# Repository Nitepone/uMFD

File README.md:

# uMFD: A small button pad for Pico

This is a version 1.0 of my small mfd controller.

This repo contains the blender files for the case, along with kicad files for
the button carrier PCB, and the source code for the gamepad software.

The completed project appears as an xinput device where each of the 20 buttons
it its own digital input.

## Building

1. `mkdir build`
2. `cmake -B build`
3. `make -C build`
4. "Where is the final image?"
5. `find -name '*.uf2'`

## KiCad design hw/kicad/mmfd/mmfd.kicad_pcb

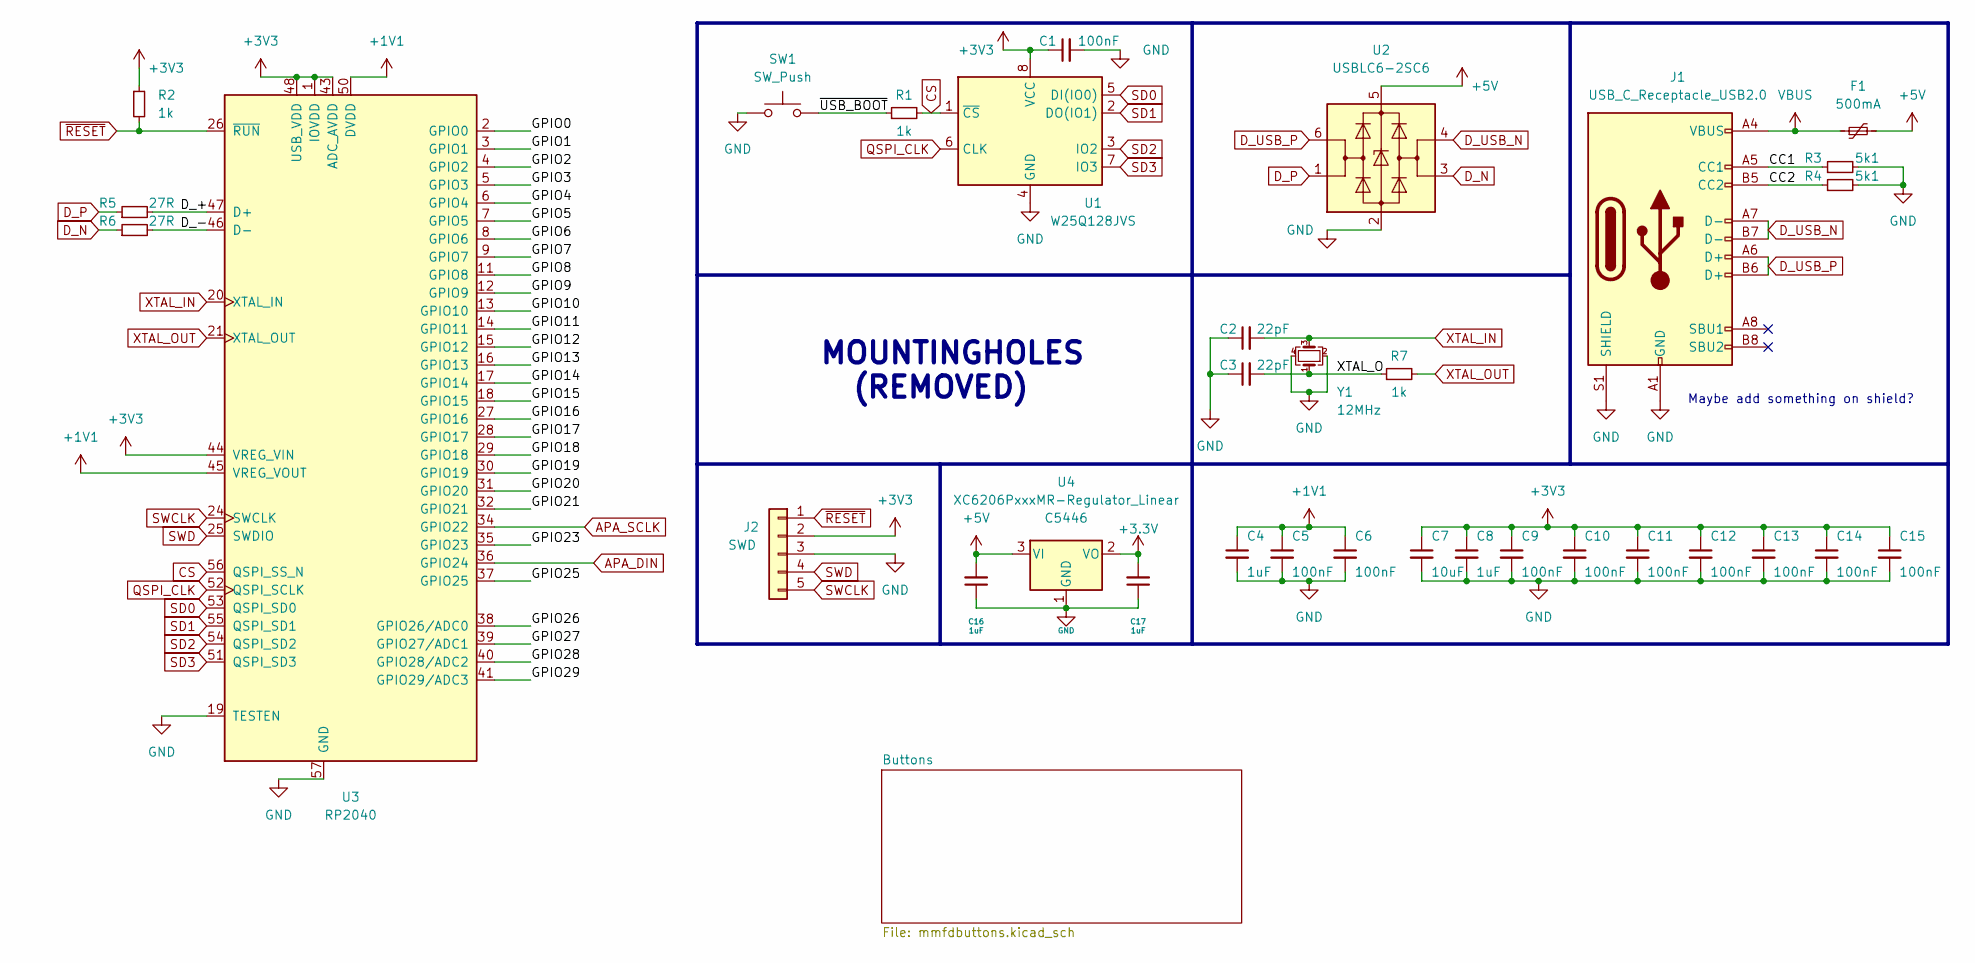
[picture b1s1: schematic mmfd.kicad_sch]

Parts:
C1, C5, C6, C9, C10, C11, C12, C13, C14, C15: 100nF; C_0402_1005Metric; LCSC C1525
C2, C3: 22pF; C_0402_1005Metric; LCSC C1555
C4, C8, C16, C17: 1uF; C_0402_1005Metric; LCSC C52923
C7: 10uF; C_0402_1005Metric; LCSC C15525
F1: 500mA; Fuse_1206_3216Metric; LCSC C70076
J1: USB_C_Receptacle_USB2.0; USB_C_Receptacle_HRO_TYPE-C-31-M-12; LCSC C165948
J2: SWD; PinSocket_1x05_P2.54mm_Vertical
R1, R2, R7: 1k; R_0402_1005Metric; LCSC C11702
R3, R4: 5k1; R_0402_1005Metric; LCSC C25905
R5, R6: 27R; R_0603_1608Metric; LCSC C25190
SW1: SW_Push; PinSocket_1x02_P2.54mm_Vertical
U1: W25Q128JVS; SOIC-8_5.23x5.23mm_P1.27mm; LCSC C131025
U2: USBLC6-2SC6; SOT-23-6; LCSC C2827654
U3: RP2040; RP2040-QFN-56; LCSC C2040
U4: XC6206PxxxMR-Regulator_Linear; SOT-23; LCSC C5446
Y1: 12MHz; Crystal_SMD_3225-4Pin_3.2x2.5mm; LCSC C9002

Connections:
+1V1: C4.1, C5.1, C6.1, U3.23 (DVDD), U3.45 (VREG_VOUT), U3.50 (DVDD)
+5V: C16.2, F1.2, U2.5 (VBUS), U4.3 (VI); also elsewhere on the board
/CC1: J1.A5 (CC1), R3.1
/CC2: J1.B5 (CC2), R4.1
/D_+: R5.2, U3.47 (D+)
/D_-: R6.2, U3.46 (D-)
/GPIO0: U3.2 (GPIO0)
/GPIO1: U3.3 (GPIO1)
/GPIO2: U3.4 (GPIO2)
/GPIO3: U3.5 (GPIO3)
/GPIO4: U3.6 (GPIO4)
/GPIO5: U3.7 (GPIO5)
/GPIO6: U3.8 (GPIO6)
/GPIO7: U3.9 (GPIO7)
/GPIO8: U3.11 (GPIO8)
/GPIO9: U3.12 (GPIO9)
/GPIO10: U3.13 (GPIO10)
/GPIO11: U3.14 (GPIO11)
/GPIO12: U3.15 (GPIO12)
/GPIO13: U3.16 (GPIO13)
/GPIO14: U3.17 (GPIO14)
/GPIO15: U3.18 (GPIO15)
/GPIO16: U3.27 (GPIO16)
/GPIO17: U3.28 (GPIO17)
/GPIO18: U3.29 (GPIO18)
/GPIO19: U3.30 (GPIO19)
/GPIO20: U3.31 (GPIO20)
/GPIO21: U3.32 (GPIO21)
/GPIO23: U3.35 (GPIO23)
/GPIO25: U3.37 (GPIO25)
/GPIO26: U3.38 (GPIO26/ADC0)
/GPIO27: U3.39 (GPIO27/ADC1)
/GPIO28: U3.40 (GPIO28/ADC2)
/GPIO29: U3.41 (GPIO29/ADC3)
/XTAL_O: C3.2, R7.1, Y1.1
APA_DIN: U3.36 (GPIO24); also elsewhere on the board
APA_SCLK: U3.34 (GPIO22); also elsewhere on the board
CS: R1.2, U1.1 (~CS), U3.56 (QSPI_SS_N)
D_N: R6.1, U2.3 (I/O2)
D_P: R5.1, U2.1 (I/O1)
D_USB_N: J1.A7 (D-), J1.B7 (D-), U2.4 (I/O2)
D_USB_P: J1.A6 (D+), J1.B6 (D+), U2.6 (I/O1)
QSPI_CLK: U1.6 (CLK), U3.52 (QSPI_SCLK)
SD0: U1.5 (DI(IO0)), U3.53 (QSPI_SD0)
SD1: U1.2 (DO(IO1)), U3.55 (QSPI_SD1)
SD2: U1.3 (IO2), U3.54 (QSPI_SD2)
SD3: U1.7 (IO3), U3.51 (QSPI_SD3)
SWCLK: J2.5, U3.24 (SWCLK)
SWD: J2.4, U3.25 (SWDIO)
VBUS: F1.1, J1.A4 (VBUS), J1.A9 (VBUS), J1.B4 (VBUS), J1.B9 (VBUS)
XTAL_IN: C2.2, U3.20 (XTAL_IN), Y1.3
XTAL_OUT: R7.2, U3.21 (XTAL_OUT)
~RESET: J2.1, R2.2, U3.26 (~RUN)

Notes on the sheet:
MOUNTINGHOLES (REMOVED)
Maybe add something on shield?

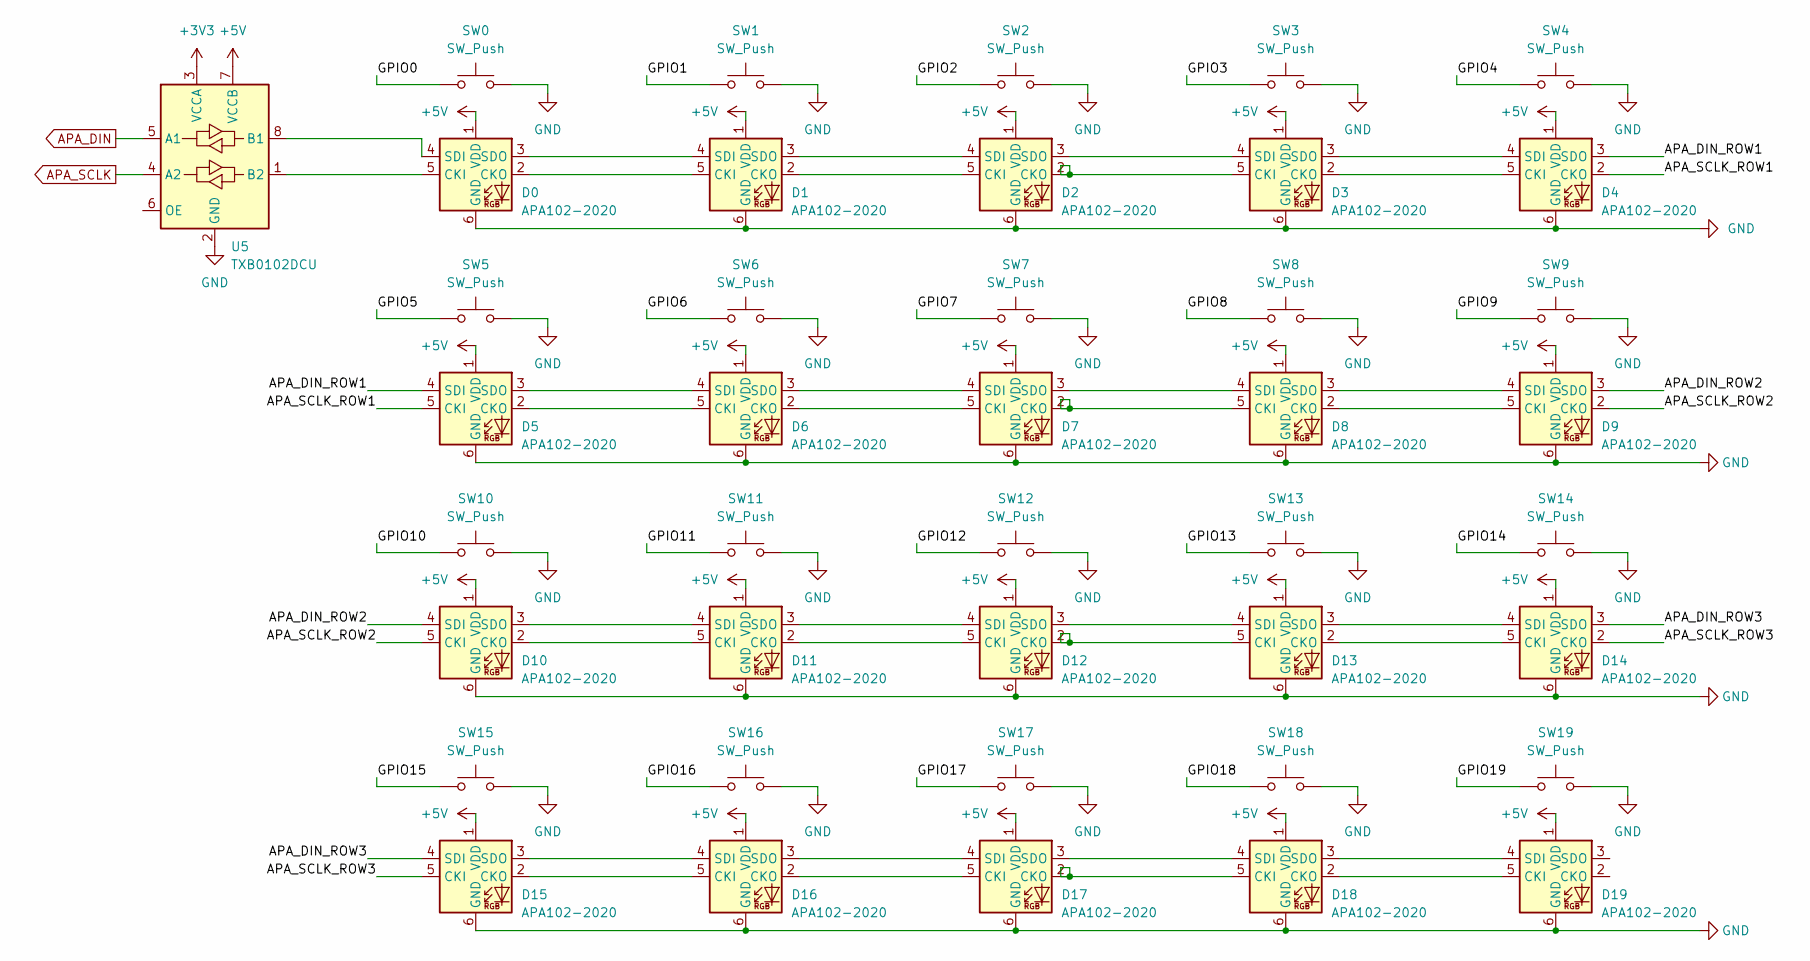
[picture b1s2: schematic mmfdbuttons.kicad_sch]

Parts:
D0, D1, D2, D3, D4, D5, D6, D7, D8, D9, D10, D11, D12, D13, D14, D15, D16, D17, D18, D19: APA102-2020; LED-APA102-2020
SW0, SW1, SW2, SW3, SW4, SW5, SW6, SW7, SW8, SW9, SW10, SW11, SW12, SW13, SW14, SW15, SW16, SW17, SW18, SW19: SW_Push; Kailh_socket_MX_optional
U5: TXB0102DCU; VSSOP-8_2.4x2.1mm_P0.5mm

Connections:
+5V: D0.1 (VDD), D1.1 (VDD), D2.1 (VDD), D3.1 (VDD), D4.1 (VDD), D5.1 (VDD), D6.1 (VDD), D7.1 (VDD), D8.1 (VDD), D9.1 (VDD), D10.1 (VDD), D11.1 (VDD), D12.1 (VDD), D13.1 (VDD), D14.1 (VDD), D15.1 (VDD), D16.1 (VDD), D17.1 (VDD), D18.1 (VDD), D19.1 (VDD), U5.7 (VCCB); also elsewhere on the board
/Buttons/APA_DIN_ROW1: D4.3 (SDO), D5.4 (SDI)
/Buttons/APA_DIN_ROW2: D9.3 (SDO), D10.4 (SDI)
/Buttons/APA_DIN_ROW3: D14.3 (SDO), D15.4 (SDI)
/Buttons/APA_SCLK_ROW1: D4.2 (CKO), D5.5 (CKI)
/Buttons/APA_SCLK_ROW2: D9.2 (CKO), D10.5 (CKI)
/Buttons/APA_SCLK_ROW3: D14.2 (CKO), D15.5 (CKI)
/Buttons/GPIO0: SW0.1
/Buttons/GPIO2: SW2.1
/Buttons/GPIO3: SW3.1
/Buttons/GPIO4: SW4.1
/Buttons/GPIO5: SW5.1
/Buttons/GPIO6: SW6.1
/Buttons/GPIO7: SW7.1
/Buttons/GPIO8: SW8.1
/Buttons/GPIO9: SW9.1
/Buttons/GPIO10: SW10.1
/Buttons/GPIO11: SW11.1
/Buttons/GPIO12: SW12.1
/Buttons/GPIO13: SW13.1
/Buttons/GPIO14: SW14.1
/Buttons/GPIO15: SW15.1
/Buttons/GPIO16: SW16.1
/Buttons/GPIO17: SW17.1
/Buttons/GPIO18: SW18.1
/Buttons/GPIO19: SW19.1
APA_DIN: U5.5 (A1); also elsewhere on the board
APA_SCLK: U5.4 (A2); also elsewhere on the board
unnamed: D0.5 (CKI), U5.1 (B2)
unnamed: D0.2 (CKO), D1.5 (CKI)
unnamed: D0.4 (SDI), U5.8 (B1)
unnamed: D0.3 (SDO), D1.4 (SDI)
unnamed: D1.2 (CKO), D2.5 (CKI)
unnamed: D1.3 (SDO), D2.4 (SDI)
unnamed: D2.2 (CKO), D3.5 (CKI)
unnamed: D2.3 (SDO), D3.4 (SDI)
unnamed: D3.2 (CKO), D4.5 (CKI)
unnamed: D3.3 (SDO), D4.4 (SDI)
unnamed: D5.2 (CKO), D6.5 (CKI)
unnamed: D5.3 (SDO), D6.4 (SDI)
unnamed: D6.2 (CKO), D7.5 (CKI)
unnamed: D6.3 (SDO), D7.4 (SDI)
unnamed: D7.2 (CKO), D8.5 (CKI)
unnamed: D7.3 (SDO), D8.4 (SDI)
unnamed: D8.2 (CKO), D9.5 (CKI)
unnamed: D8.3 (SDO), D9.4 (SDI)
unnamed: D10.2 (CKO), D11.5 (CKI)
unnamed: D10.3 (SDO), D11.4 (SDI)
unnamed: D11.2 (CKO), D12.5 (CKI)
unnamed: D11.3 (SDO), D12.4 (SDI)
unnamed: D12.2 (CKO), D13.5 (CKI)
unnamed: D12.3 (SDO), D13.4 (SDI)
unnamed: D13.2 (CKO), D14.5 (CKI)
unnamed: D13.3 (SDO), D14.4 (SDI)
unnamed: D15.2 (CKO), D16.5 (CKI)
unnamed: D15.3 (SDO), D16.4 (SDI)
unnamed: D16.2 (CKO), D17.5 (CKI)
unnamed: D16.3 (SDO), D17.4 (SDI)
unnamed: D17.2 (CKO), D18.5 (CKI)
unnamed: D17.3 (SDO), D18.4 (SDI)
unnamed: D18.2 (CKO), D19.5 (CKI)
unnamed: D18.3 (SDO), D19.4 (SDI)

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
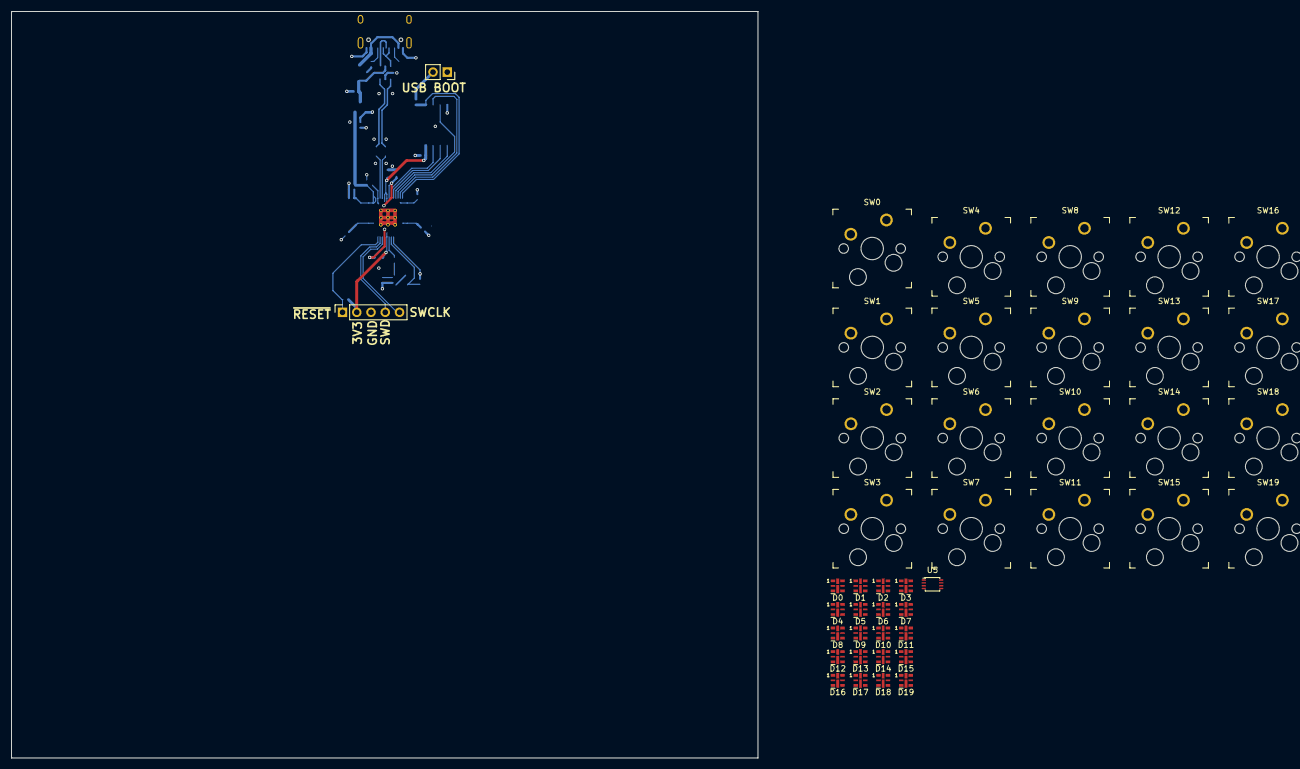
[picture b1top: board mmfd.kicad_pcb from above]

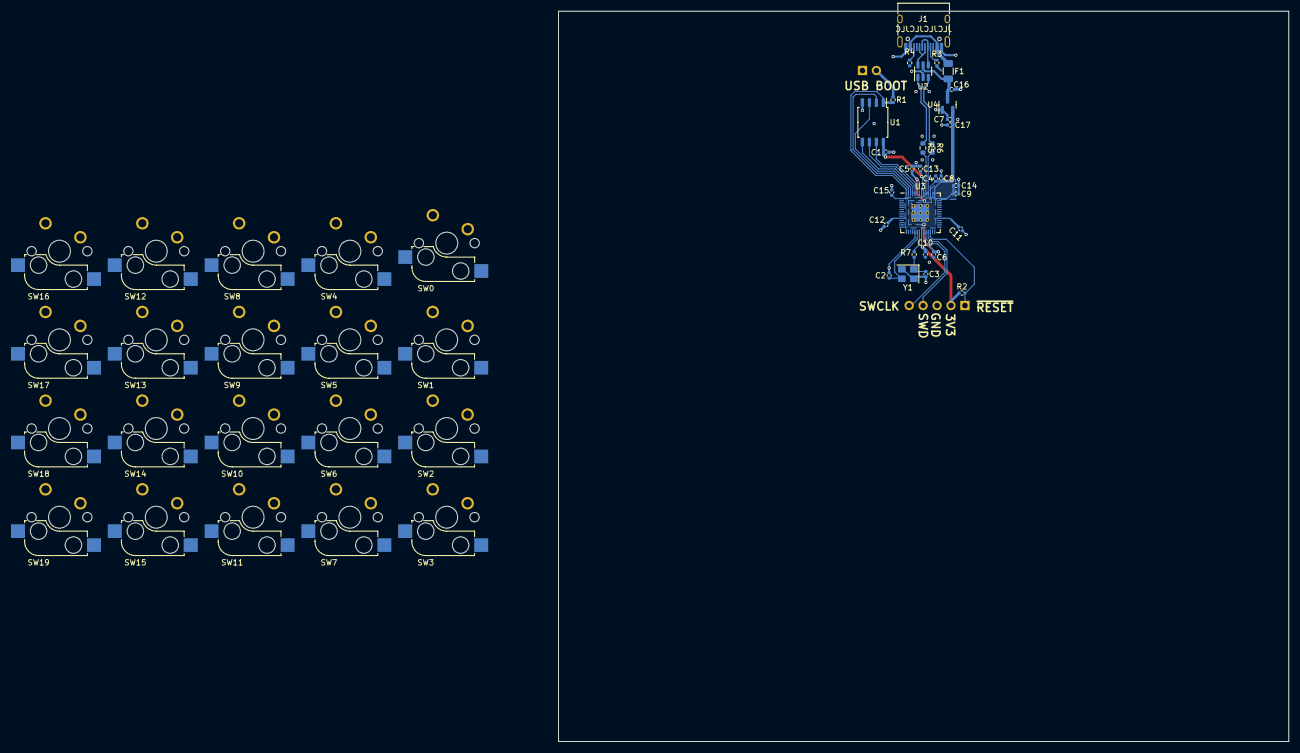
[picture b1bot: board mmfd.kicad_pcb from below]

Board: 2 copper layers, 133.0 x 133.0 mm, 74 parts (31 on the bottom side), 68 nets.

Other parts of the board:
SW20: SW_Push; PinSocket_1x02_P2.54mm_Vertical

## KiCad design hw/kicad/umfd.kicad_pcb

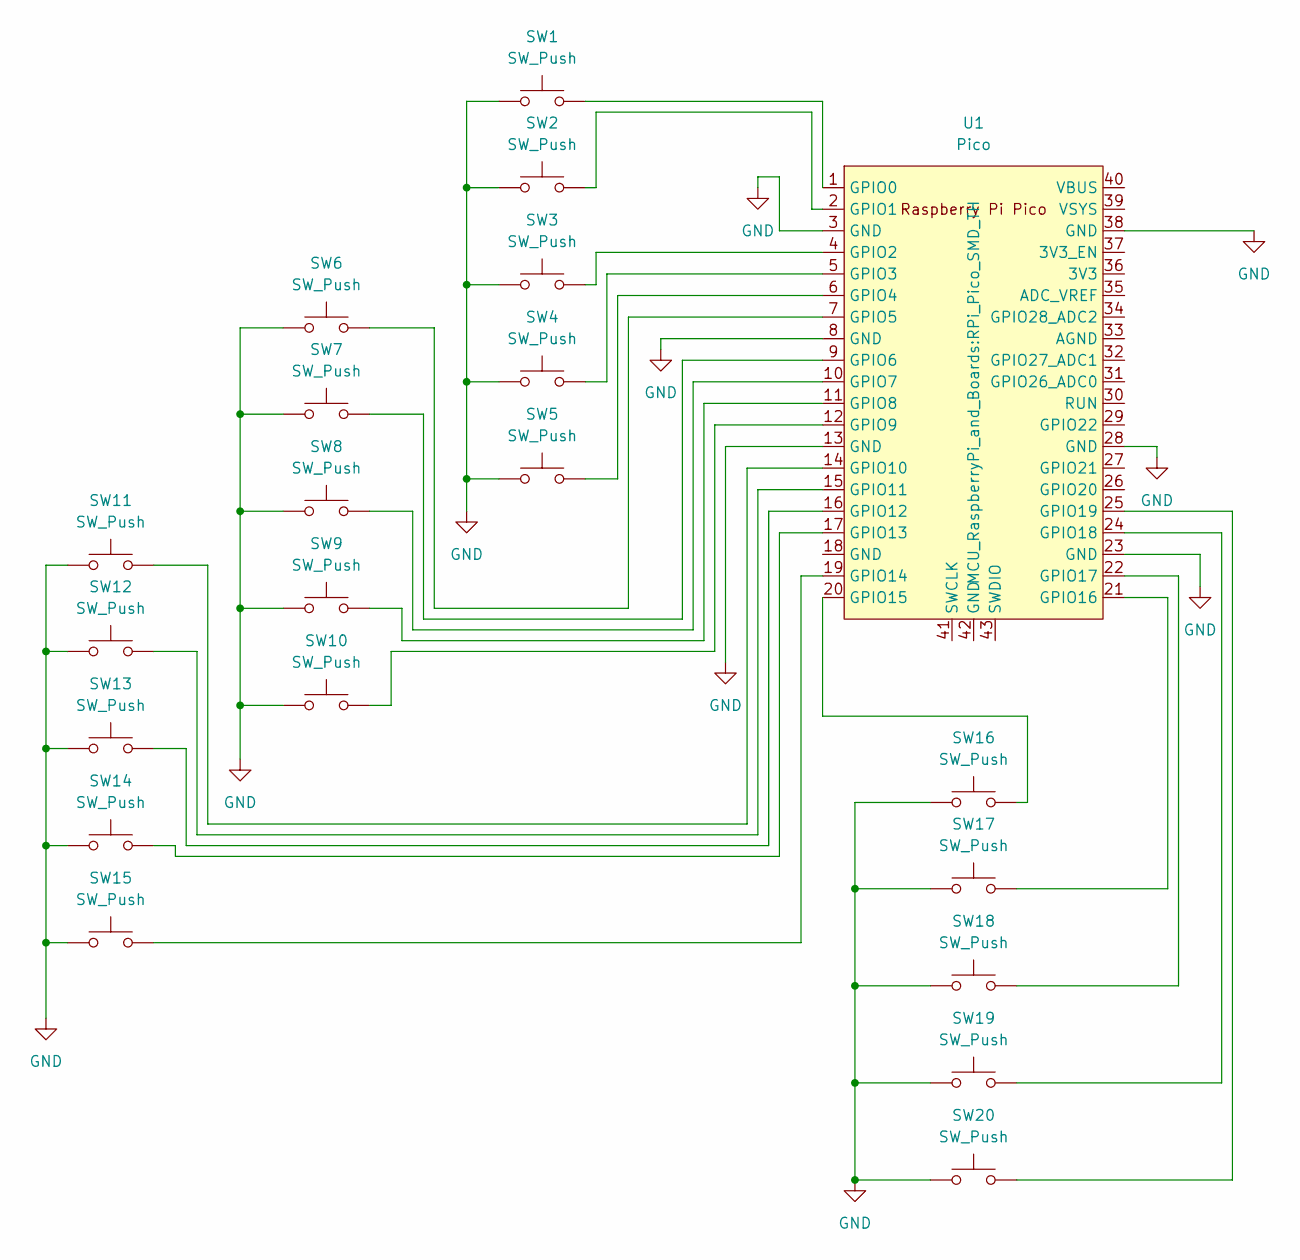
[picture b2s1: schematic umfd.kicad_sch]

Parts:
SW1, SW2, SW3, SW4, SW5, SW6, SW7, SW8, SW9, SW10, SW11, SW12, SW13, SW14, SW15, SW16, SW17, SW18, SW19, SW20: SW_Push; SW_PUSH_6mm
U1: Pico; RPi_Pico_SMD_TH

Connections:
GND: SW1.1, SW2.1, SW3.1, SW4.1, SW5.1, SW6.1, SW7.1, SW8.1, SW9.1, SW10.1, SW11.1, SW12.1, SW13.1, SW14.1, SW15.1, SW16.1, SW17.1, SW18.1, SW19.1, SW20.1, U1.3 (GND), U1.8 (GND), U1.13 (GND), U1.23 (GND), U1.28 (GND), U1.38 (GND)
unnamed: SW1.2, U1.1 (GPIO0)
unnamed: SW2.2, U1.2 (GPIO1)
unnamed: SW3.2, U1.4 (GPIO2)
unnamed: SW4.2, U1.5 (GPIO3)
unnamed: SW5.2, U1.6 (GPIO4)
unnamed: SW6.2, U1.7 (GPIO5)
unnamed: SW7.2, U1.9 (GPIO6)
unnamed: SW8.2, U1.10 (GPIO7)
unnamed: SW9.2, U1.11 (GPIO8)
unnamed: SW10.2, U1.12 (GPIO9)
unnamed: SW11.2, U1.14 (GPIO10)
unnamed: SW12.2, U1.15 (GPIO11)
unnamed: SW13.2, U1.16 (GPIO12)
unnamed: SW14.2, U1.17 (GPIO13)
unnamed: SW15.2, U1.19 (GPIO14)
unnamed: SW16.2, U1.20 (GPIO15)
unnamed: SW17.2, U1.21 (GPIO16)
unnamed: SW18.2, U1.22 (GPIO17)
unnamed: SW19.2, U1.24 (GPIO18)
unnamed: SW20.2, U1.25 (GPIO19)

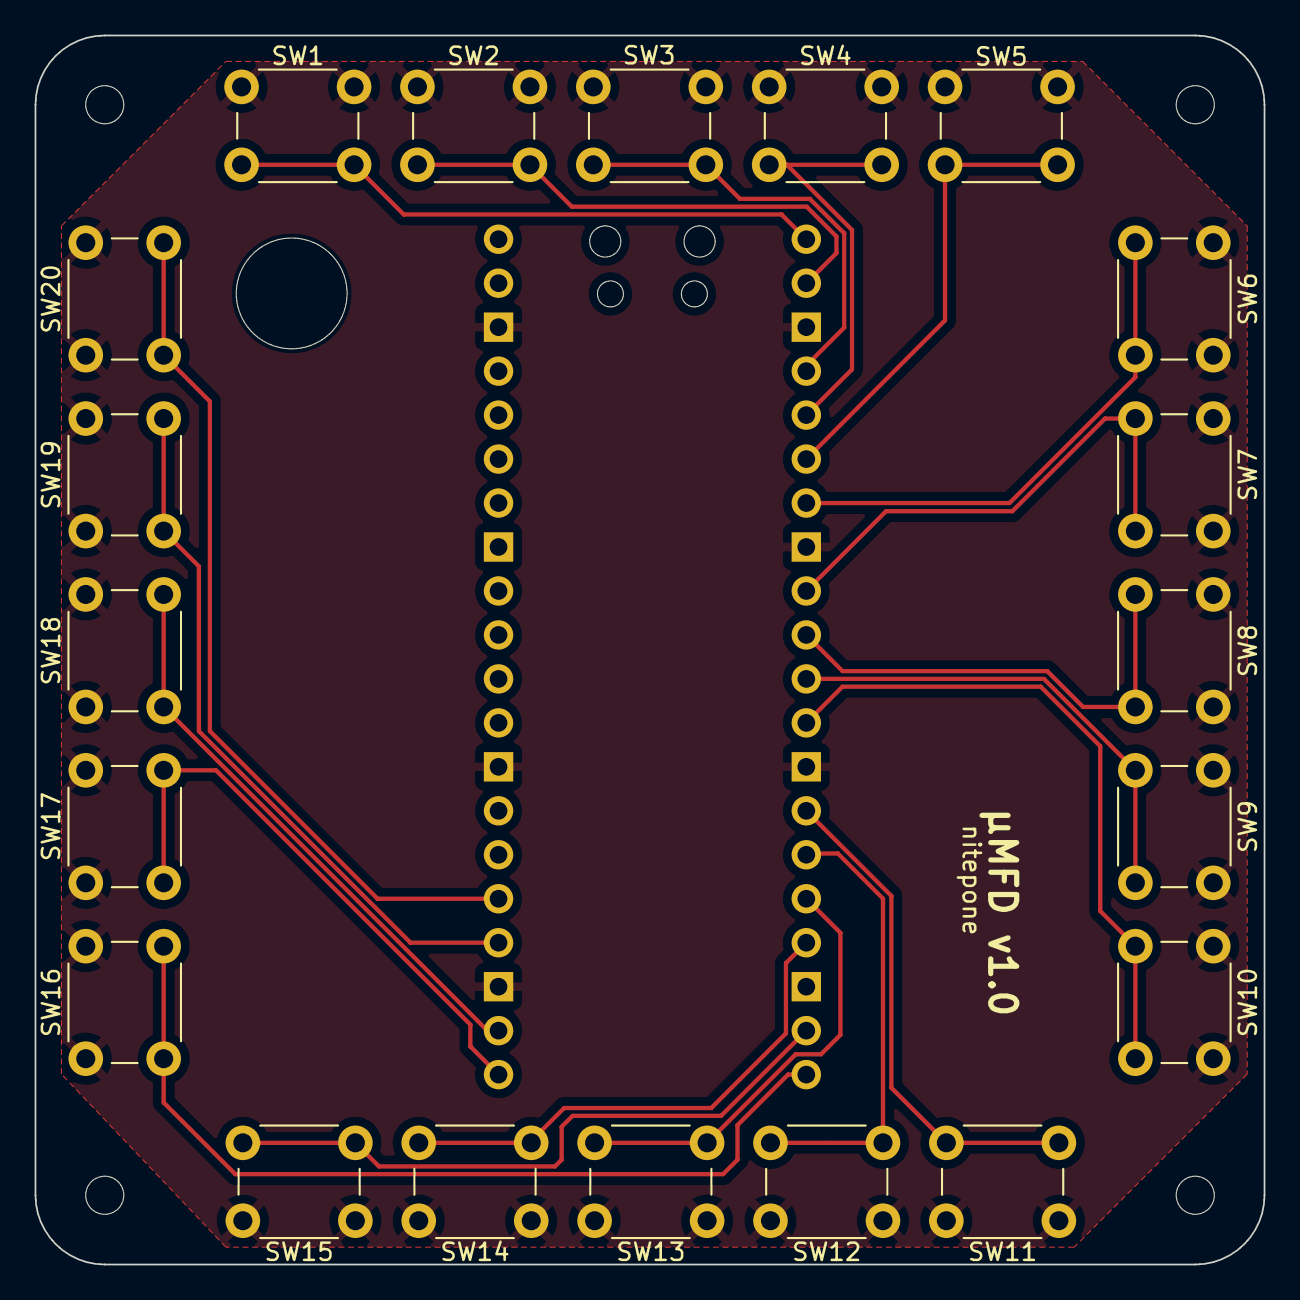
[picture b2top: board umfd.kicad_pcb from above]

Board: 2 copper layers, 71.0 x 71.0 mm, 26 parts (1 on the bottom side), 21 nets.

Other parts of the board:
hole: MountingHole_6.4mm_M6_ISO14580
m1, m2, m3, m4: MountingHole_2.2mm_M2

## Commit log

2022-04-29 Initial Commit
    - Source dir with HID example
    - clang-format config
    - llvm with more 4 tabs
    - Pico-sdk as submodule
2022-04-29 Reformat the world
2022-04-30 Very bad IRQ based gamepad for PM Uni
2022-05-15 Switch to gpio polling. Remove old crap.
2023-06-25 Modify for uMFD prototype
2023-06-25 Add Readme
2025-04-08 Finish v1.0
    Uploads all the files used to complete the v1.0 milestone.
    This has been complete for a while now.. but just uploading them.
